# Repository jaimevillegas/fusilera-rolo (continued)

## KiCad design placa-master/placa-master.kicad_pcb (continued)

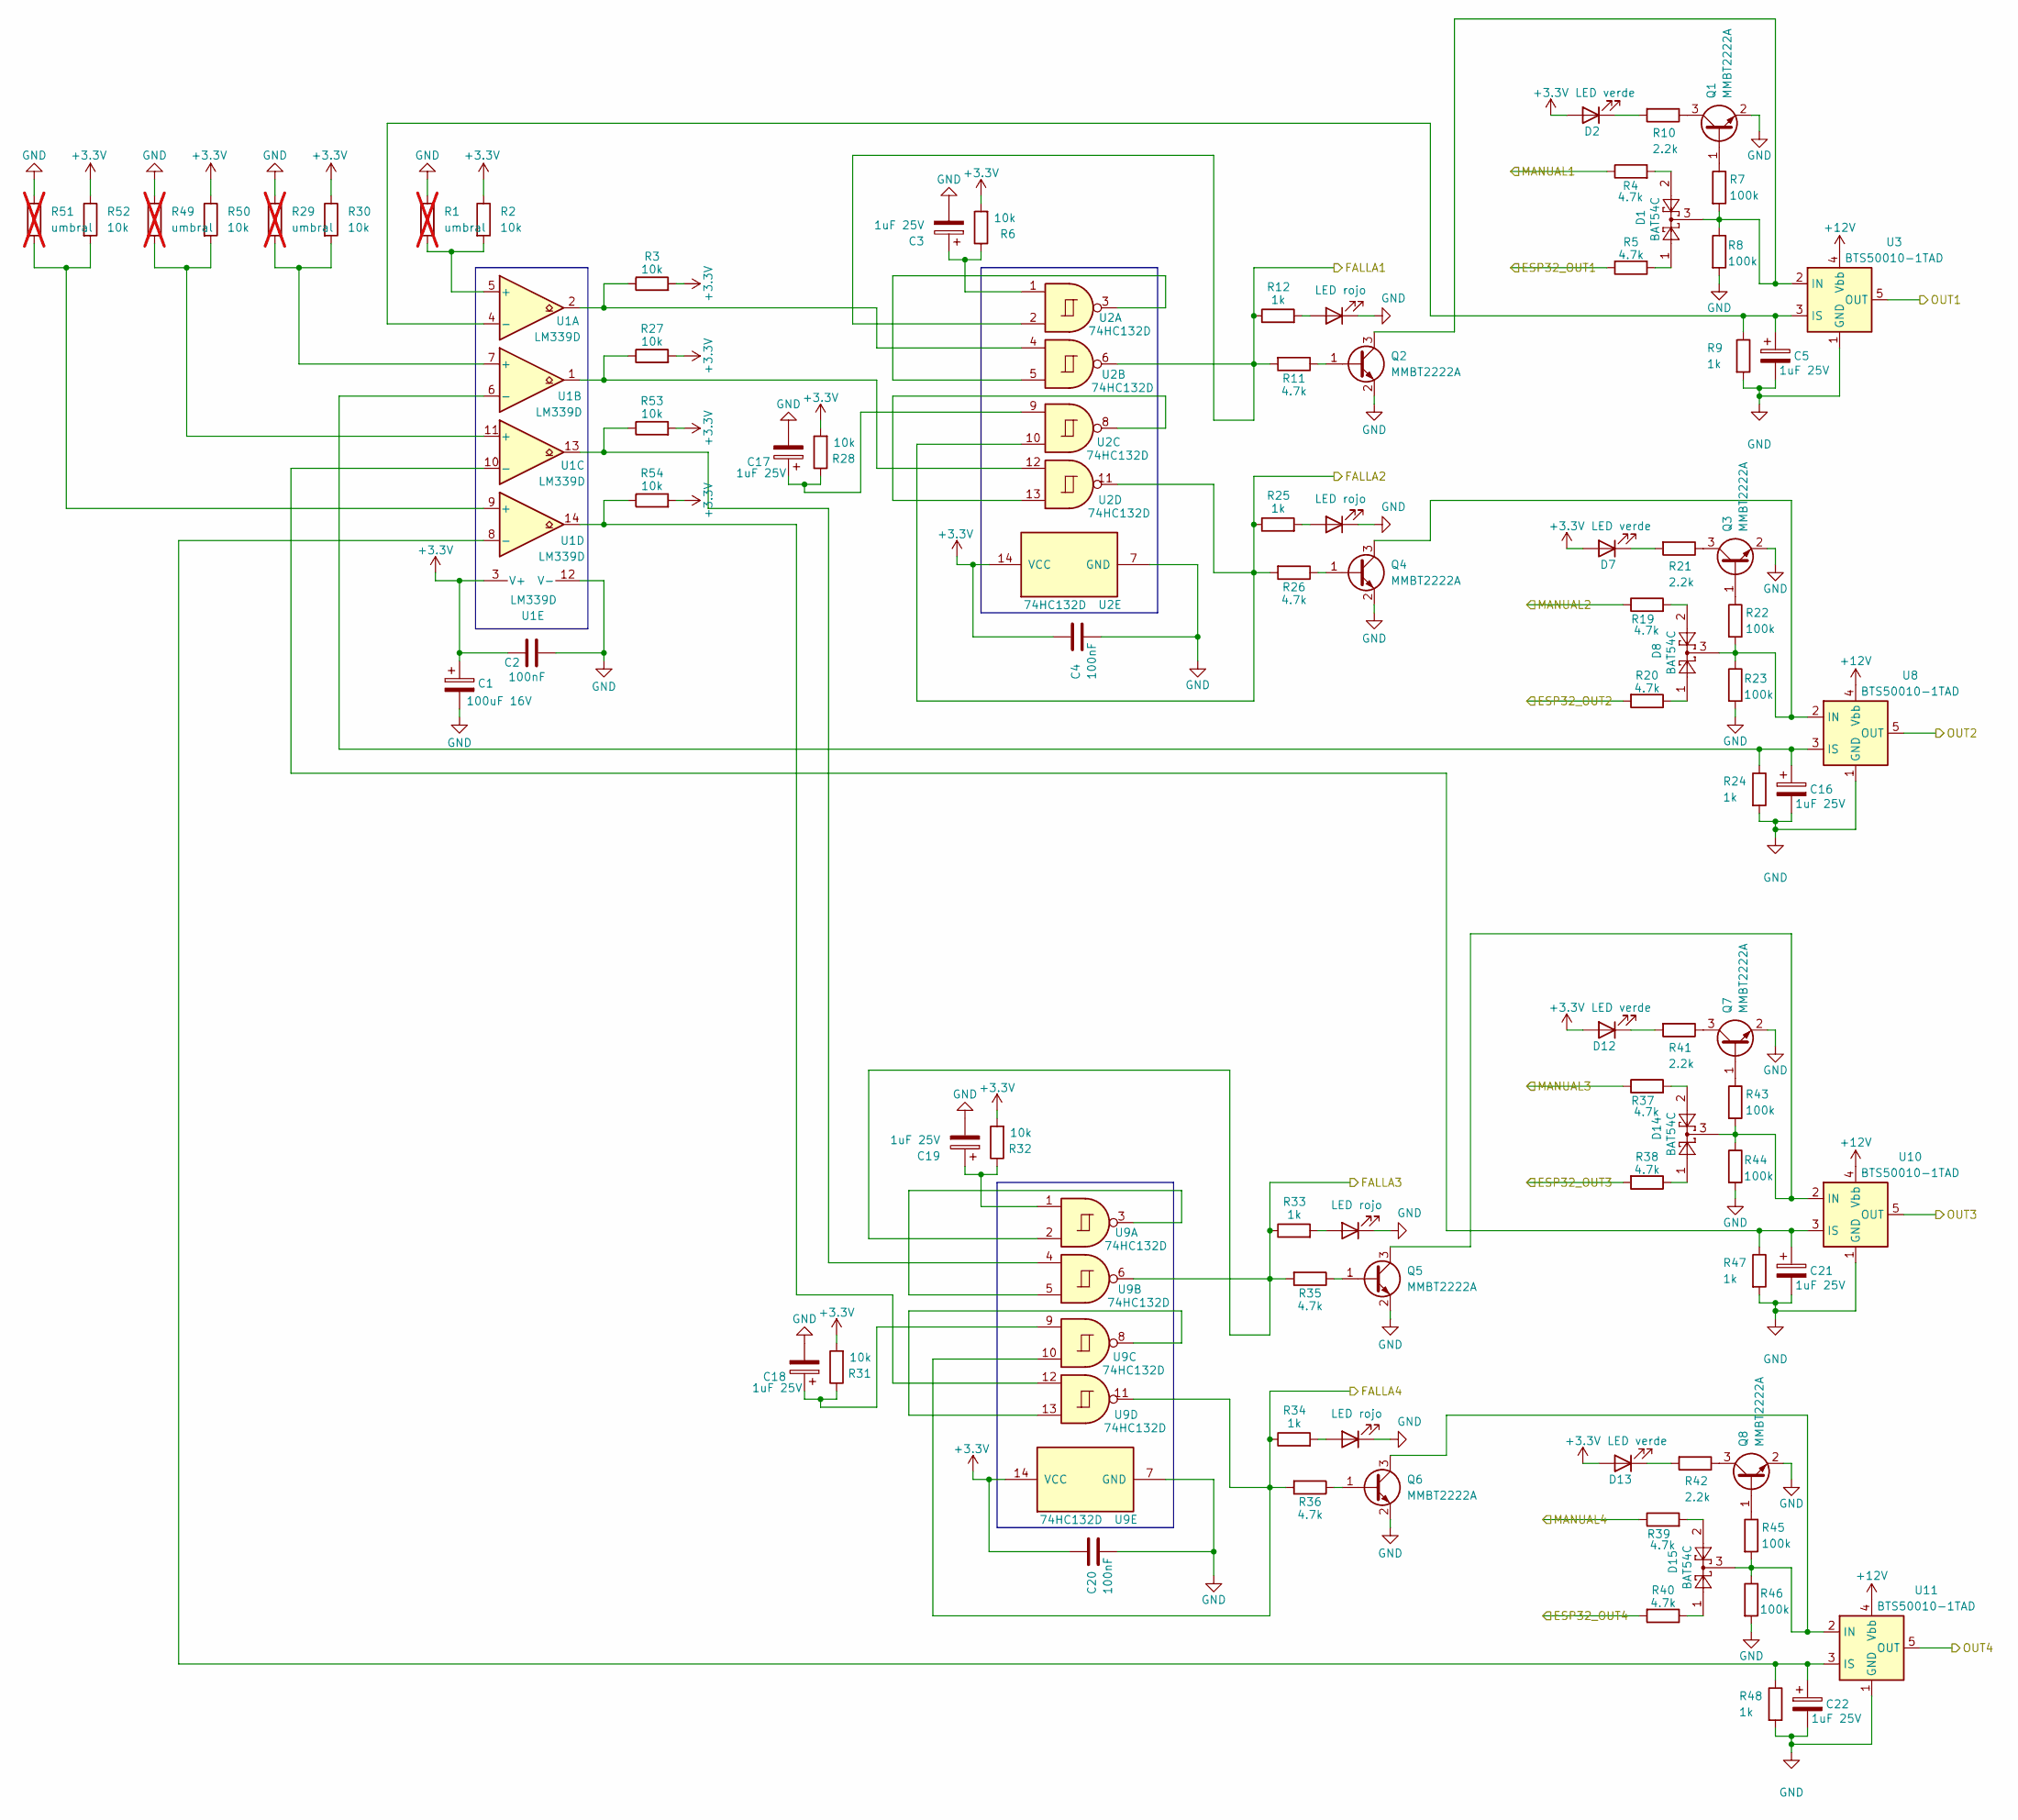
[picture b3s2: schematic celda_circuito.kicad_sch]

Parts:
C1: 100uF 16V; CP_Elec_6.3x5.4
C2, C4, C20: 100nF; C_0805_2012Metric
C3, C5, C16, C17, C18, C19, C21, C22: 1uF 25V; CP_Elec_4x5.4
D1, D8, D14, D15: BAT54C; SOT-23
D2, D7, D12, D13: LED verde; LED_0805_2012Metric
D3, D9, D10, D11: LED rojo; LED_0805_2012Metric
Q1, Q2, Q3, Q4, Q5, Q6, Q7, Q8: MMBT2222A; SOT-23
R1, R29, R49, R51: umbral; R_Axial_DIN0207_L6.3mm_D2.5mm_P10.16mm_Horizontal; not fitted
R2, R3, R6, R27, R28, R30, R31, R32, R50, R52, R53, R54: 10k; R_0805_2012Metric
R4, R5, R11, R19, R20, R26, R35, R36, R37, R38, R39, R40: 4.7k; R_0805_2012Metric
R7, R8, R22, R23, R43, R44, R45, R46: 100k; R_0805_2012Metric
R9, R12, R24, R25, R33, R34, R47, R48: 1k; R_0805_2012Metric
R10, R21, R41, R42: 2.2k; R_0805_2012Metric
U1: LM339D; SOIC-14_3.9x8.7mm_P1.27mm
U2, U9: 74HC132D; SOIC-14_3.9x8.7mm_P1.27mm
U3, U8, U10, U11: BTS50010-1TAD; TO-263-7_TabPin4

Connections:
+3.3V: C1.1, C2.1, C4.1, C20.1, D2.2 (A), D7.2 (A), D12.2 (A), D13.2 (A), R2.1, R3.2, R6.2, R27.2, R28.2, R30.1, R31.2, R32.2, R50.1, R52.1, R53.2, R54.2, U1.3 (V+), U2.14 (VCC), U9.14 (VCC); also elsewhere on the board
+12V: U3.4 (Vbb), U8.4 (Vbb), U10.4 (Vbb), U11.4 (Vbb); also elsewhere on the board
/ESP32_OUT1: R5.2; also elsewhere on the board
/ESP32_OUT2: R20.2; also elsewhere on the board
/ESP32_OUT3: R38.2; also elsewhere on the board
/ESP32_OUT4: R40.2; also elsewhere on the board
/FALLA1: R11.2, R12.1, U2.2, U2.6; also elsewhere on the board
/FALLA2: R25.1, R26.2, U2.10, U2.11; also elsewhere on the board
/FALLA3: R33.1, R35.2, U9.2, U9.6; also elsewhere on the board
/FALLA4: R34.1, R36.2, U9.10, U9.11; also elsewhere on the board
/MANUAL1: R4.1; also elsewhere on the board
/MANUAL2: R19.1; also elsewhere on the board
/MANUAL3: R37.1; also elsewhere on the board
/MANUAL4: R39.1; also elsewhere on the board
/OUT1: U3.5 (OUT), U3.6 (OUT), U3.7 (OUT); also elsewhere on the board
/OUT2: U8.5 (OUT), U8.6 (OUT), U8.7 (OUT); also elsewhere on the board
/OUT3: U10.5 (OUT), U10.6 (OUT), U10.7 (OUT); also elsewhere on the board
/OUT4: U11.5 (OUT), U11.6 (OUT), U11.7 (OUT); also elsewhere on the board
GND: C1.2, C2.2, C3.2, C4.2, C5.2, C16.2, C17.2, C18.2, C19.2, C20.2, C21.2, C22.2, D3.1 (K), D9.1 (K), D10.1 (K), D11.1 (K), Q1.2 (E), Q2.2 (E), Q3.2 (E), Q4.2 (E), Q5.2 (E), Q6.2 (E), Q7.2 (E), Q8.2 (E), R1.1, R8.2, R9.2, R23.2, R24.2, R29.1, R44.2, R46.2, R47.2, R48.2, R49.1, R51.1, U1.12 (V-), U2.7 (GND), U3.1 (GND), U8.1 (GND), U9.7 (GND), U10.1 (GND), U11.1 (GND); also elsewhere on the board
unnamed: C3.1, R6.1, U2.1
unnamed: C17.1, R28.1, U2.9
unnamed: C18.1, R31.1, U9.9
unnamed: C19.1, R32.1, U9.1
unnamed: D1.1, R5.1
unnamed: D1.2, R4.2
unnamed: D2.1 (K), R10.2
unnamed: D3.2 (A), R12.2
unnamed: D7.1 (K), R21.2
unnamed: D8.1, R20.1
unnamed: D8.2, R19.2
unnamed: D9.2 (A), R25.2
unnamed: D10.2 (A), R33.2
unnamed: D11.2 (A), R34.2
unnamed: D12.1 (K), R41.2
unnamed: D13.1 (K), R42.2
unnamed: D14.1, R38.1
unnamed: D14.2, R37.2
unnamed: D15.1, R40.1
unnamed: D15.2, R39.2
unnamed: Q1.1 (B), R7.1
unnamed: Q1.3 (C), R10.1
unnamed: Q2.1 (B), R11.1
unnamed: D1.3, Q2.3 (C), R7.2, R8.1, U3.2 (IN)
unnamed: Q3.1 (B), R22.1
unnamed: Q3.3 (C), R21.1
unnamed: Q4.1 (B), R26.1
unnamed: D8.3, Q4.3 (C), R22.2, R23.1, U8.2 (IN)
unnamed: Q5.1 (B), R35.1
unnamed: D14.3, Q5.3 (C), R43.2, R44.1, U10.2 (IN)
unnamed: Q6.1 (B), R36.1
unnamed: D15.3, Q6.3 (C), R45.2, R46.1, U11.2 (IN)
unnamed: Q7.1 (B), R43.1
unnamed: Q7.3 (C), R41.1
unnamed: Q8.1 (B), R45.1
unnamed: Q8.3 (C), R42.1
unnamed: R3.1, U1.2, U2.4
unnamed: R27.1, U1.1, U2.12
unnamed: R53.1, U1.13, U9.4
unnamed: R54.1, U1.14, U9.12
unnamed: R1.2, R2.2, U1.5 (+)
unnamed: C5.1, R9.1, U1.4 (-), U3.3 (IS)
unnamed: R29.2, R30.2, U1.7 (+)
unnamed: C16.1, R24.1, U1.6 (-), U8.3 (IS)
unnamed: R49.2, R50.2, U1.11 (+)
unnamed: R51.2, R52.2, U1.9 (+)
unnamed: U2.3, U2.5
unnamed: U2.8, U2.13
unnamed: U9.3, U9.5
unnamed: U9.8, U9.13
unnamed: C21.1, R47.1, U1.10 (-), U10.3 (IS)
unnamed: C22.1, R48.1, U1.8 (-), U11.3 (IS)

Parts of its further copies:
C101, C201: 100uF 16V; CP_Elec_6.3x5.4
C102, C104, C120, C202, C204, C220: 100nF; C_0805_2012Metric
C103, C105, C116, C117, C118, C119, C121, C122, C203, C205, C216, C217, C218, C219, C221, C222: 1uF 25V; CP_Elec_4x5.4
D101, D108, D114, D115, D201, D208, D214, D215: BAT54C; SOT-23
D102, D107, D112, D113, D202, D207, D212, D213: LED verde; LED_0805_2012Metric
D103, D109, D110, D111, D203, D209, D210, D211: LED rojo; LED_0805_2012Metric
Q101, Q102, Q103, Q104, Q105, Q106, Q107, Q108, Q201, Q202, Q203, Q204, Q205, Q206, Q207, Q208: MMBT2222A; SOT-23
R101, R129, R149, R151, R201, R229, R249, R251: umbral; R_Axial_DIN0207_L6.3mm_D2.5mm_P10.16mm_Horizontal; not fitted
R102, R103, R106, R127, R128, R130, R131, R132, R150, R152, R153, R154, R202, R203, R206, R227, R228, R230, R231, R232, R250, R252, R253, R254: 10k; R_0805_2012Metric
R104, R105, R111, R119, R120, R126, R135, R136, R137, R138, R139, R140, R204, R205, R211, R219, R220, R226, R235, R236, R237, R238, R239, R240: 4.7k; R_0805_2012Metric
R107, R108, R122, R123, R143, R144, R145, R146, R207, R208, R222, R223, R243, R244, R245, R246: 100k; R_0805_2012Metric
R109, R112, R124, R125, R133, R134, R147, R148, R209, R212, R224, R225, R233, R234, R247, R248: 1k; R_0805_2012Metric
R110, R121, R141, R142, R210, R221, R241, R242: 2.2k; R_0805_2012Metric
U101, U201: LM339D; SOIC-14_3.9x8.7mm_P1.27mm
U102, U109, U202, U209: 74HC132D; SOIC-14_3.9x8.7mm_P1.27mm
U103, U108, U110, U111, U203, U208, U210, U211: BTS50010-1TAD; TO-263-7_TabPin4

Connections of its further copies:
+3.3V: C101.1, C102.1, C104.1, C120.1, C201.1, C202.1, C204.1, C220.1, D102.2 (A), D107.2 (A), D112.2 (A), D113.2 (A), D202.2 (A), D207.2 (A), D212.2 (A), D213.2 (A), R102.1, R103.2, R106.2, R127.2, R128.2, R130.1, R131.2, R132.2, R150.1, R152.1, R153.2, R154.2, R202.1, R203.2, R206.2, R227.2, R228.2, R230.1, R231.2, R232.2, R250.1, R252.1, R253.2, R254.2, U101.3 (V+), U102.14 (VCC), U109.14 (VCC), U201.3 (V+), U202.14 (VCC), U209.14 (VCC); also elsewhere on the board
+12V: U103.4 (Vbb), U108.4 (Vbb), U110.4 (Vbb), U111.4 (Vbb), U203.4 (Vbb), U208.4 (Vbb), U210.4 (Vbb), U211.4 (Vbb); also elsewhere on the board
/ESP32_OUT5: R105.2; also elsewhere on the board
/ESP32_OUT6: R120.2; also elsewhere on the board
/ESP32_OUT7: R138.2; also elsewhere on the board
/ESP32_OUT8: R140.2; also elsewhere on the board
/ESP32_OUT9: R205.2; also elsewhere on the board
/ESP32_OUT10: R220.2; also elsewhere on the board
/ESP32_OUT11: R238.2; also elsewhere on the board
/ESP32_OUT12: R240.2; also elsewhere on the board
/FALLA5: R111.2, R112.1, U102.2, U102.6; also elsewhere on the board
/FALLA6: R125.1, R126.2, U102.10, U102.11; also elsewhere on the board
/FALLA7: R133.1, R135.2, U109.2, U109.6; also elsewhere on the board
/FALLA8: R134.1, R136.2, U109.10, U109.11; also elsewhere on the board
/FALLA9: R211.2, R212.1, U202.2, U202.6; also elsewhere on the board
/FALLA10: R225.1, R226.2, U202.10, U202.11; also elsewhere on the board
/FALLA11: R233.1, R235.2, U209.2, U209.6; also elsewhere on the board
/FALLA12: R234.1, R236.2, U209.10, U209.11; also elsewhere on the board
/MANUAL5: R104.1; also elsewhere on the board
/MANUAL6: R119.1; also elsewhere on the board
/MANUAL7: R137.1; also elsewhere on the board
/MANUAL8: R139.1; also elsewhere on the board
/MANUAL9: R204.1; also elsewhere on the board
/MANUAL10: R219.1; also elsewhere on the board
/MANUAL11: R237.1; also elsewhere on the board
/MANUAL12: R239.1; also elsewhere on the board
/OUT5: U103.5 (OUT), U103.6 (OUT), U103.7 (OUT); also elsewhere on the board
/OUT6: U108.5 (OUT), U108.6 (OUT), U108.7 (OUT); also elsewhere on the board
/OUT7: U110.5 (OUT), U110.6 (OUT), U110.7 (OUT); also elsewhere on the board
/OUT8: U111.5 (OUT), U111.6 (OUT), U111.7 (OUT); also elsewhere on the board
/OUT9: U203.5 (OUT), U203.6 (OUT), U203.7 (OUT); also elsewhere on the board
/OUT10: U208.5 (OUT), U208.6 (OUT), U208.7 (OUT); also elsewhere on the board
/OUT11: U210.5 (OUT), U210.6 (OUT), U210.7 (OUT); also elsewhere on the board
/OUT12: U211.5 (OUT), U211.6 (OUT), U211.7 (OUT); also elsewhere on the board
GND: C101.2, C102.2, C103.2, C104.2, C105.2, C116.2, C117.2, C118.2, C119.2, C120.2, C121.2, C122.2, C201.2, C202.2, C203.2, C204.2, C205.2, C216.2, C217.2, C218.2, C219.2, C220.2, C221.2, C222.2, D103.1 (K), D109.1 (K), D110.1 (K), D111.1 (K), D203.1 (K), D209.1 (K), D210.1 (K), D211.1 (K), Q101.2 (E), Q102.2 (E), Q103.2 (E), Q104.2 (E), Q105.2 (E), Q106.2 (E), Q107.2 (E), Q108.2 (E), Q201.2 (E), Q202.2 (E), Q203.2 (E), Q204.2 (E), Q205.2 (E), Q206.2 (E), Q207.2 (E), Q208.2 (E), R101.1, R108.2, R109.2, R123.2, R124.2, R129.1, R144.2, R146.2, R147.2, R148.2, R149.1, R151.1, R201.1, R208.2, R209.2, R223.2, R224.2, R229.1, R244.2, R246.2, R247.2, R248.2, R249.1, R251.1, U101.12 (V-), U102.7 (GND), U103.1 (GND), U108.1 (GND), U109.7 (GND), U110.1 (GND), U111.1 (GND), U201.12 (V-), U202.7 (GND), U203.1 (GND), U208.1 (GND), U209.7 (GND), U210.1 (GND), U211.1 (GND); also elsewhere on the board
unnamed: C103.1, R106.1, U102.1
unnamed: C117.1, R128.1, U102.9
unnamed: C118.1, R131.1, U109.9
unnamed: C119.1, R132.1, U109.1
unnamed: C203.1, R206.1, U202.1
unnamed: C217.1, R228.1, U202.9
unnamed: C218.1, R231.1, U209.9
unnamed: C219.1, R232.1, U209.1
unnamed: D101.1, R105.1
unnamed: D101.2, R104.2
unnamed: D102.1 (K), R110.2
unnamed: D103.2 (A), R112.2
unnamed: D107.1 (K), R121.2
unnamed: D108.1, R120.1
unnamed: D108.2, R119.2
unnamed: D109.2 (A), R125.2
unnamed: D110.2 (A), R133.2
unnamed: D111.2 (A), R134.2
unnamed: D112.1 (K), R141.2
unnamed: D113.1 (K), R142.2
unnamed: D114.1, R138.1
unnamed: D114.2, R137.2
unnamed: D115.1, R140.1
unnamed: D115.2, R139.2
unnamed: D201.1, R205.1
unnamed: D201.2, R204.2
unnamed: D202.1 (K), R210.2
unnamed: D203.2 (A), R212.2
unnamed: D207.1 (K), R221.2
unnamed: D208.1, R220.1
unnamed: D208.2, R219.2
unnamed: D209.2 (A), R225.2
unnamed: D210.2 (A), R233.2
unnamed: D211.2 (A), R234.2
unnamed: D212.1 (K), R241.2
unnamed: D213.1 (K), R242.2
unnamed: D214.1, R238.1
unnamed: D214.2, R237.2
unnamed: D215.1, R240.1
unnamed: D215.2, R239.2
unnamed: Q101.1 (B), R107.1
unnamed: Q101.3 (C), R110.1
unnamed: Q102.1 (B), R111.1
unnamed: D101.3, Q102.3 (C), R107.2, R108.1, U103.2 (IN)
unnamed: Q103.1 (B), R122.1
unnamed: Q103.3 (C), R121.1
unnamed: Q104.1 (B), R126.1
unnamed: D108.3, Q104.3 (C), R122.2, R123.1, U108.2 (IN)
unnamed: Q105.1 (B), R135.1
unnamed: D114.3, Q105.3 (C), R143.2, R144.1, U110.2 (IN)
unnamed: Q106.1 (B), R136.1
unnamed: D115.3, Q106.3 (C), R145.2, R146.1, U111.2 (IN)
unnamed: Q107.1 (B), R143.1
unnamed: Q107.3 (C), R141.1
unnamed: Q108.1 (B), R145.1
unnamed: Q108.3 (C), R142.1
unnamed: Q201.1 (B), R207.1
unnamed: Q201.3 (C), R210.1
unnamed: Q202.1 (B), R211.1
unnamed: D201.3, Q202.3 (C), R207.2, R208.1, U203.2 (IN)
unnamed: Q203.1 (B), R222.1
unnamed: Q203.3 (C), R221.1
unnamed: Q204.1 (B), R226.1
unnamed: D208.3, Q204.3 (C), R222.2, R223.1, U208.2 (IN)
unnamed: Q205.1 (B), R235.1
unnamed: D214.3, Q205.3 (C), R243.2, R244.1, U210.2 (IN)
unnamed: Q206.1 (B), R236.1
unnamed: D215.3, Q206.3 (C), R245.2, R246.1, U211.2 (IN)
unnamed: Q207.1 (B), R243.1
unnamed: Q207.3 (C), R241.1
unnamed: Q208.1 (B), R245.1
unnamed: Q208.3 (C), R242.1
unnamed: R103.1, U101.2, U102.4
unnamed: R127.1, U101.1, U102.12
unnamed: R153.1, U101.13, U109.4
unnamed: R154.1, U101.14, U109.12
unnamed: R203.1, U201.2, U202.4
unnamed: R227.1, U201.1, U202.12
unnamed: R253.1, U201.13, U209.4
unnamed: R254.1, U201.14, U209.12
unnamed: R101.2, R102.2, U101.5 (+)
unnamed: C105.1, R109.1, U101.4 (-), U103.3 (IS)
unnamed: R129.2, R130.2, U101.7 (+)
unnamed: C116.1, R124.1, U101.6 (-), U108.3 (IS)
unnamed: R149.2, R150.2, U101.11 (+)
unnamed: C121.1, R147.1, U101.10 (-), U110.3 (IS)
unnamed: R151.2, R152.2, U101.9 (+)
unnamed: C122.1, R148.1, U101.8 (-), U111.3 (IS)
unnamed: U102.3, U102.5
unnamed: U102.8, U102.13
unnamed: U109.3, U109.5
unnamed: U109.8, U109.13
unnamed: R201.2, R202.2, U201.5 (+)
unnamed: C205.1, R209.1, U201.4 (-), U203.3 (IS)
unnamed: R229.2, R230.2, U201.7 (+)
unnamed: C216.1, R224.1, U201.6 (-), U208.3 (IS)
unnamed: R249.2, R250.2, U201.11 (+)
unnamed: C221.1, R247.1, U201.10 (-), U210.3 (IS)
unnamed: R251.2, R252.2, U201.9 (+)
unnamed: C222.1, R248.1, U201.8 (-), U211.3 (IS)
unnamed: U202.3, U202.5
unnamed: U202.8, U202.13
unnamed: U209.3, U209.5
unnamed: U209.8, U209.13

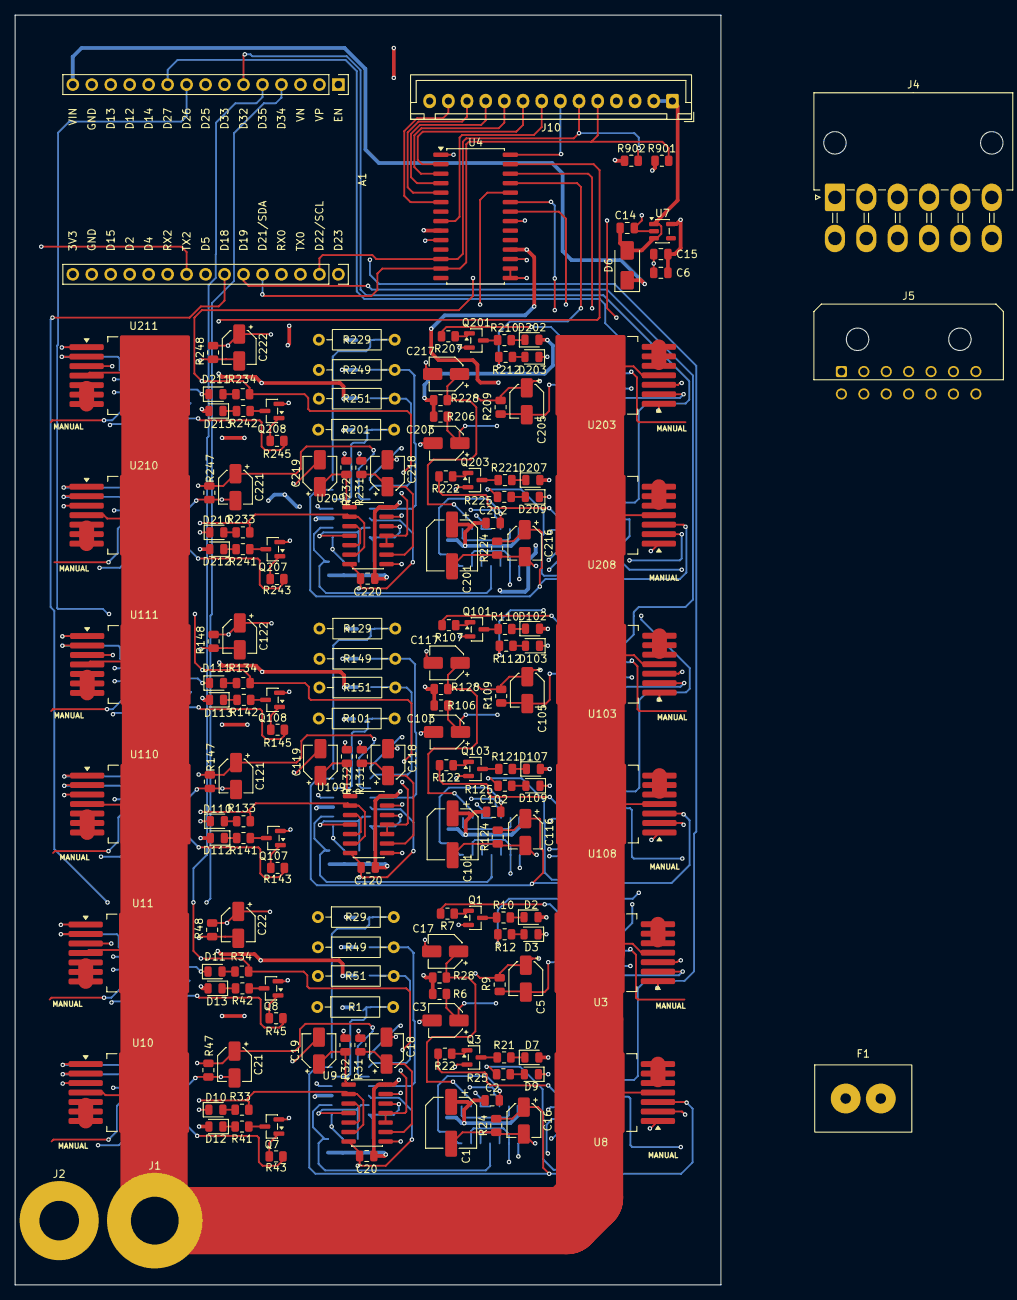
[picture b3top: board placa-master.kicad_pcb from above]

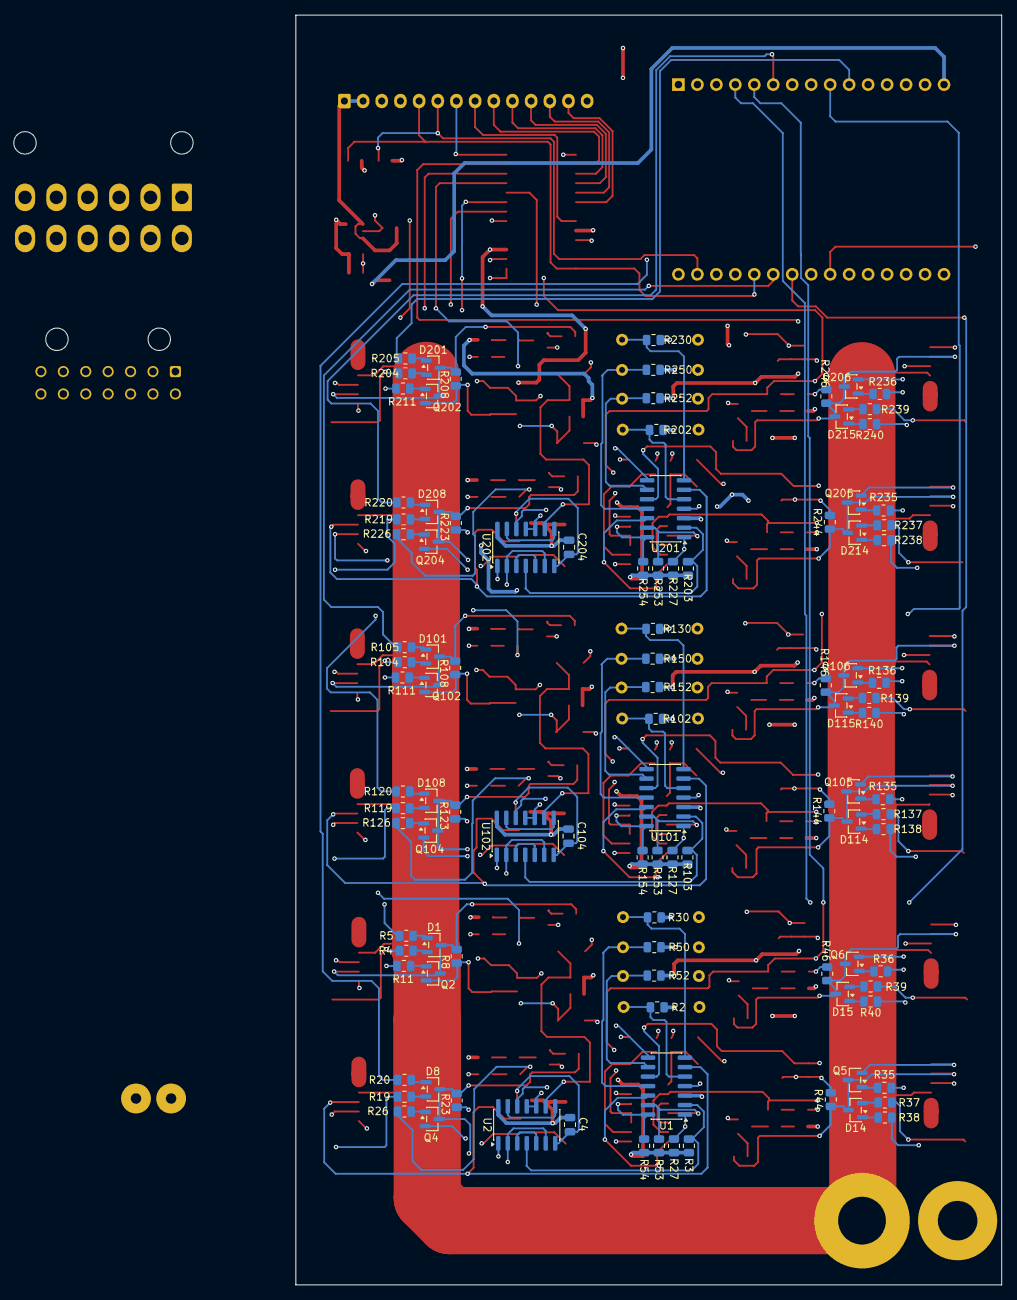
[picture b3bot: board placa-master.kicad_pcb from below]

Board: 4 copper layers, 94.5 x 170.0 mm, 276 parts (105 on the bottom side), 219 nets.

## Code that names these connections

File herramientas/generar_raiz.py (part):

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    2: "FALLA1", 3: "FALLA2", 4: "FALLA3", 5: "FALLA4",
    17: "SCL", 20: "SDA",
}
U4_PINS = {**{21 + i: f"FALLA{5 + i}" for i in range(7)}, 1: "FALLA12",
           28: "ESP32_OUT15", 8: "ESP32_OUT16", 2: "ESP32_OUT17",
           3: "ESP32_OUT18", 4: "ESP32_OUT19", 5: "FALLA27", 6: "FALLA28"}
U5_PINS = {**{21 + i: f"FALLA{13 + i}" for i in range(7)},
           **{1 + i: f"FALLA{20 + i}" for i in range(7)},
           28: "ESP32_OUT13", 8: "ESP32_OUT14"}
LINK_PINS = ["LINK_5V", "LINK_5V", "GND", "GND", "SDA", "SCL",
             "ESP32_OUT15", "ESP32_OUT16", "ESP32_OUT17", "ESP32_OUT18",
             "ESP32_OUT19", "FALLA27", "FALLA28", None]  # 14: reserva

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    # --- microcontrolador / MCP ----------------------------------------
    if board == "master":
        s, _ = part("A1", "A1", 218.44, 69.85)
        body += s + tie(pins_esp, 218.44, 69.85, {**ESP32_MASTER, 14: "GND", 29: "GND", 15: "VIN_ESP32"},
                        nc=[1, 11, 12, 18, 19, 23, 27, 28, 30])
        s, _ = part("U4", "U4", 218.44, 149.86)
        body += s + tie(pins_mcp, 218.44, 149.86,
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            body += s + tie(pins_r, x, 195.58, {1: "+3.3V", 2: net})
        # LDO 3,3 V de la master (entrada: LINK_5V desde la slave) y diodo hacia VIN del ESP32
        s, _ = part("U7", "U7", 285.75, 201.93)
        body += s + tie(pins_ldo, 285.75, 201.93, {1: "LINK_5V", 3: "LINK_5V", 2: "GND", 5: "+3.3V"}, nc=[4])
        s, _ = part("C14", "C14", 266.7, 201.93)
        body += s + tie(pins_c, 266.7, 201.93, {1: "LINK_5V", 2: "GND"})
        s, _ = part("C15", "C15", 304.8, 201.93)
        body += s + tie(pins_c, 304.8, 201.93, {1: "+3.3V", 2: "GND"})
        s, rot = part("D6", "D6", 266.7, 228.6)
        body += s + tie(pins_d, 266.7, 228.6, {2: "LINK_5V", 1: "VIN_ESP32"}, rot=rot)
        # entradas de +12 V y masa propias de la placa
        s, rot = part("J1", "J1", 266.7, 254.0)
        body += s + tie(pins_term, 266.7, 254.0, {1: "VIN_BORNE"}, rot=rot)
        # fusible master del cliente (portafusibles de 40 A sobre dos pestañas Faston .187) entre el borne y las tiras
        body += new_part("Device:Fuse", "F1", "Portafusibles 40A", "fusilera:FuseHolder_2xFaston187_P4.70mm", 292.1, 279.4, pins_f) \
            + tie(pins_f, 292.1, 279.4, {1: "VIN_BORNE", 2: "+12V"})
        s, rot = part("J2", "J2", 266.7, 266.7)
        body += s + tie(pins_term, 266.7, 266.7, {1: "GND"}, rot=rot)
        for net, fx, local in (("+12V", 292.1, False), ("GND", 304.8, False), ("LINK_5V", 317.5, True), ("VIN_ESP32", 330.2, True)):
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                ys = [float(a or c) for a, c in re.findall(r"\(xy [-\d.]+ ([-\d.]+)\)|\(at [-\d.]+ ([-\d.]+)", b)]
                if not (ys and max(ys) < 100):
                    continue
                if n == "label" and b.split('"')[1] in ("VIN_ESP32", "VBB", "V3V3_OUT"):
                    continue
                if n == "wire":
                    xy = {(float(a), float(c)) for a, c in re.findall(r"\(xy ([-\d.]+) ([-\d.]+)\)", b)}
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        body += wire(36.83, 27.94, 36.83, 25.4) + lab("VIN_BORNE", 36.83, 25.4, 0, -1)       # borne J1
        body += wire(39.37, 27.94, 39.37, 25.4) + psym("+12V", 39.37, 25.4)                  # F2 (lógica) cuelga después de F1
        body += new_part("Device:Fuse", "F1", "Portafusibles 40A", "fusilera:FuseHolder_2xFaston187_P4.70mm", 25.4, 55.88, pins_f) \
            + tie(pins_f, 25.4, 55.88, {1: "VIN_BORNE", 2: "+12V"})
        body += wire(222.25, 60.96, 222.25, 63.5) + psym("+3.3V", 222.25, 60.96)
        body += flag("+12V", 60.96, 15.24)
        # --- interruptor de +3,3 V comandado por la línea de 12 V de la llave (IGN) --------------
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        pins_dd = LibPins(get_lib(lib_text, "Device:D"))
        pins_f = LibPins(get_lib(lib_text, "Device:Fuse"))
        s, rot = part("J2", "J3", 266.7, 254.0, "borne M3 IGN")
        body += s.replace("MountingHole_5.3mm_M5_Pad", "MountingHole_3.2mm_M3_Pad") + tie(pins_term, 266.7, 254.0, {1: "IGN"}, rot=rot)
        s, rot = part("F2", "F901", 292.1, 254.0, "500mA")      # F2 viene girado 90°: aquí se coloca sin giro
        s = re.sub(r"\(at 292\.1 254 90\)", "(at 292.1 254 0)", s, count=1)
        body += s + tie(pins_f, 292.1, 254.0, {1: "IGN", 2: "IGN_F"})
        body += new_part("Device:D", "D901", "1N4148W", "Diode_SMD:D_SOD-123", 317.5, 254.0, pins_dd) \
            + tie(pins_dd, 317.5, 254.0, {2: "IGN_F", 1: "IGN_D"})
        for ref, x, y, v, mp in (("R904", 342.9, 254.0, "100k", {1: "IGN_D", 2: "IGN_B"}),
                                 ("R905", 368.3, 254.0, "47k", {1: "IGN_B", 2: "GND"}),
                                 ("R903", 317.5, 228.6, "100k", {1: "+3.3V", 2: "GATE_SW"})):
            s, rot = part("R17", ref, x, y, v)
            body += s + tie(pins_r, x, y, mp, rot=rot)
        body += new_part("Transistor_BJT:MMBT2222A", "Q902", "MMBT2222A", "Package_TO_SOT_SMD:SOT-23", 292.1, 228.6, pins_q) \
            + tie(pins_q, 292.1, 228.6, {1: "IGN_B", 2: "GND", 3: "GATE_SW"})
        body += new_part("Transistor_FET:AO3401A", "Q901", "AO3401A", "Package_TO_SOT_SMD:SOT-23", 342.9, 228.6, pins_p) \
            + tie(pins_p, 342.9, 228.6, {1: "GATE_SW", 2: "+3.3V", 3: "3V3_IGN"})
        body += flag("3V3_IGN", 368.3, 228.6, True)
    # --- conectores de E/S hacia el arnés: J4 salidas BTS (Mini-Fit Jr) y J5 manuales (Micro-Fit 3.0) ----
    chs = [4 * (k - 1) + j for k in cfg["cells"] for j in range(1, 5)]
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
